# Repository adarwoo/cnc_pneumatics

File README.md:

# cnc_pneumatic
HUB for Masso based CNC to control the pneumatics of the CNC with 1 controller which implements the logic controller, and 1 hub, which handled all the pneumatic valves.

The PCB is double sided with a ATMEL attiny1626 microcontroller in the controller and a 824 in the hub.

This simple project is for my CNC which now has a pneumatic door (operated by pneumatic cylinders) and a pneumatic valve.
The valve is a 5/3 solenoid with an exhaust center.
This means than the solenoid takes 2 inputs:
- To push the cylinder
- To pull the cylinder
- If both are on - nothing happend
- When both are off - the pressure drops in the cylinder which can be freely moved (manual door opening/closing)

A pair of microswitch/proximity sensor detect when the door is fully opened and fully closed.

The intention is to use an ATTiny microcontroller.

The firwmware is using a priority based round-robin reactor and a C++ template based state machine - the boost SML.

It will be coded in C++2017 using the avr-gcc compiler.

## The project can compile in AVR Studio, but also on a Linux box, or Windows PC.

## Draft notes:

### States
The state machine should have the following states:

- Initial
  - From boot
- Unknown
  - Door is in the air (not in closed nor fully opened position)
- Opened
  - The door is resting in the opened position. From there, it can only be closed
- Closed
  - The door is resting fully closed.
- Opening
  - The solenoid 'push' is on, and the cylinder is expected to push the door open
- Closing
  - The 'pull' solenoid is on and the cylinder is expected to pull the door closed

### Events (transitions)

- OnOpen
  - The filtered open signal goes from low to high
- OnClose
  - The open signal goes from high to low
- DoorIsUp : Upper door sensor (filtered) goes high (from low)
- DoorIsDown : Lower door sensor goes high (from low)
- Timeout : A valid timer has expired

### Actions (thing to do in states or transition)

- Push : Turn on the solenoid valve controlling the push motion of the cylinder
- Pull : Turn on the solenoid valve controlling the pull motion of the cylinder
- StartTimer : Start the timer which limits to time to wait for a cycle completion (open/close)
- ResetTimer : Invalidate any ongoing timer so when the timer expires, it does nothing
- Release : Turn off the solenoid valve (push and pull)

**Note:** Since the operation is managed by a reactor, there are no race conditions.

```mermaid
---
title: Door control
---
stateDiagram-v2

   unknown --> opened  : door_is_up
   unknown --> closed  : door_is_down
   closed  --> opening : open / push_on
   opened  --> closing : close
   opening --> opening : door_moving_up
   opening --> unknown : timeout
   opening --> opened  : door_is_up
   closing --> closing : door_moving_down
   closing --> unknown : timeout
   closing --> closed  : door_is_down
```

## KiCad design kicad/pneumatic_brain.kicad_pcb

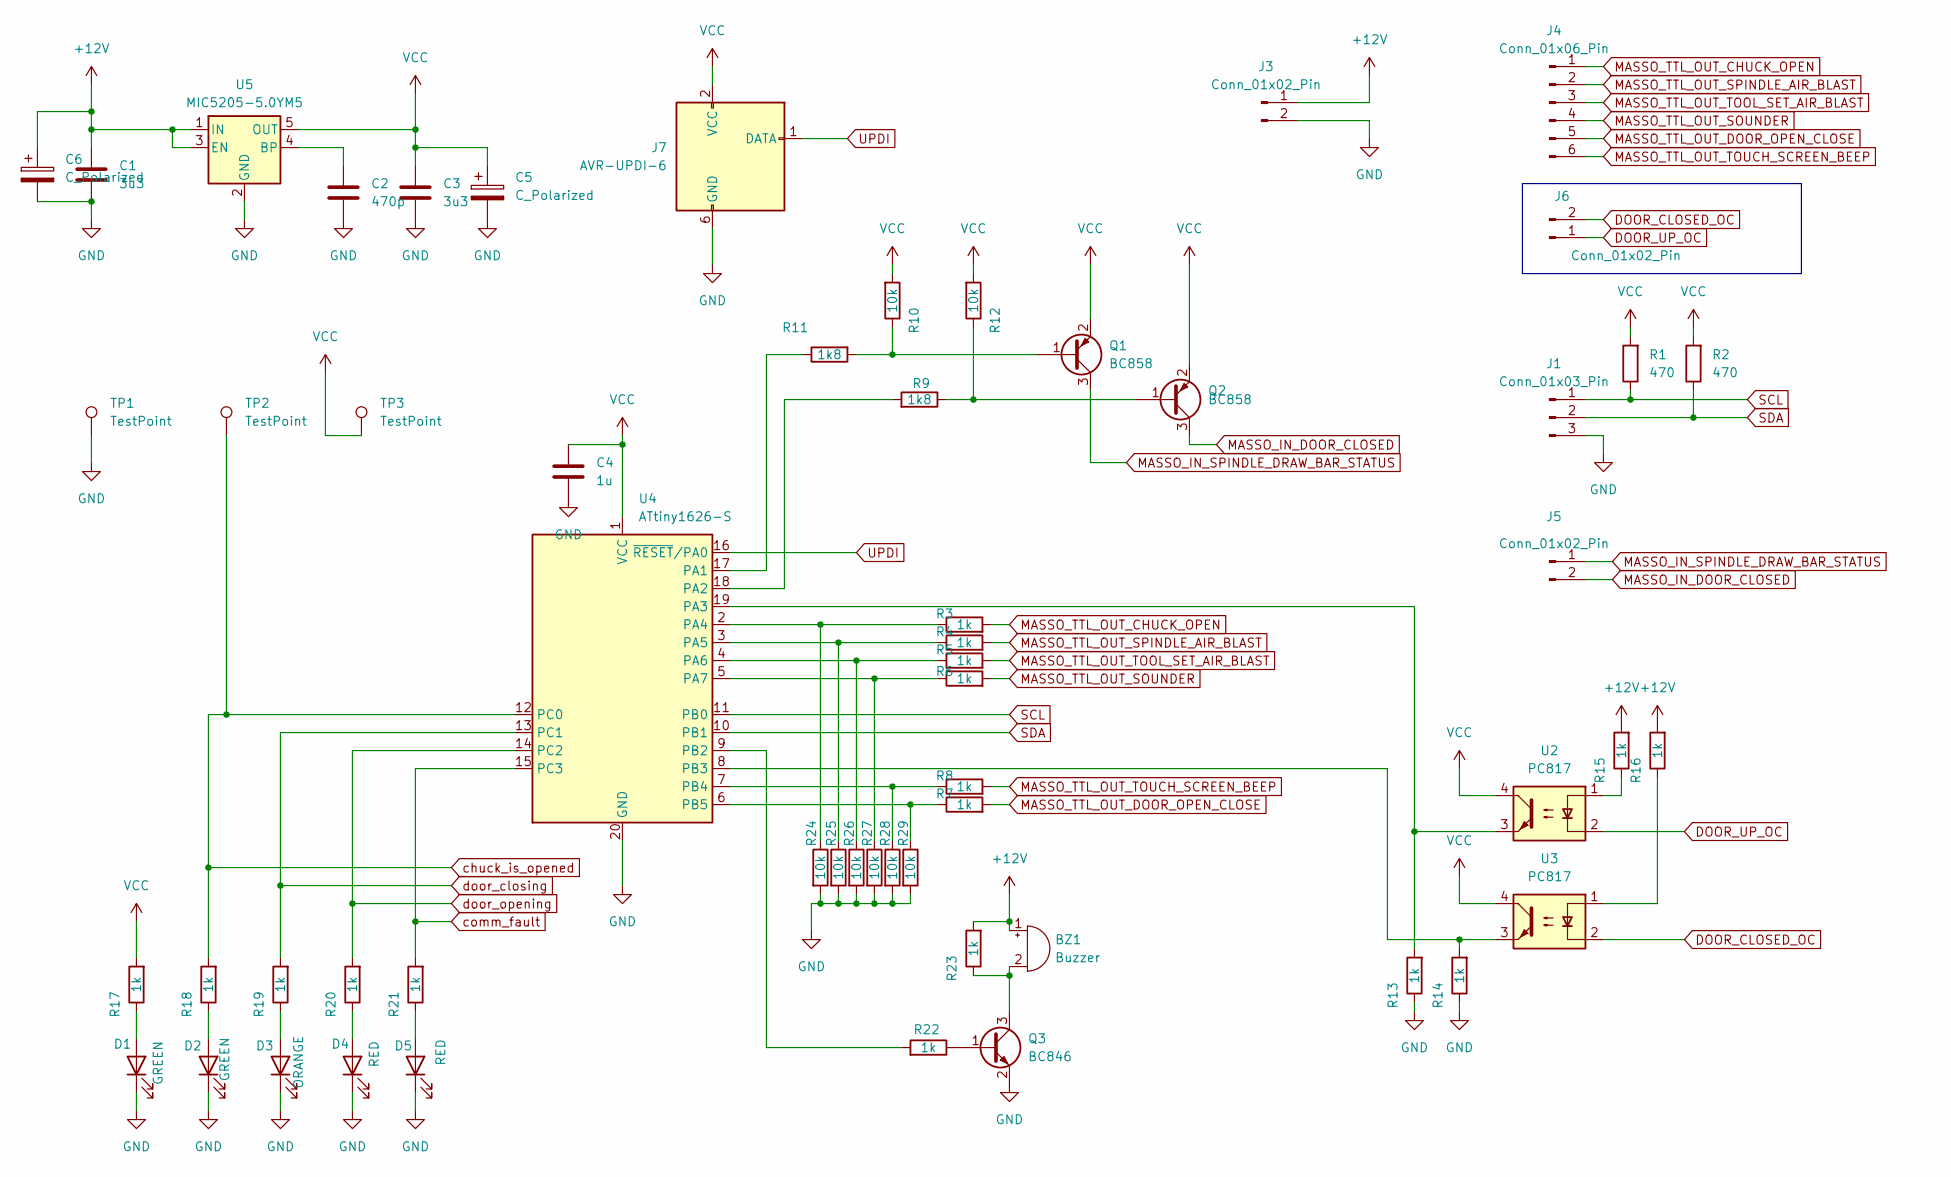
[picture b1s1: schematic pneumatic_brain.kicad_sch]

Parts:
BZ1: Buzzer; Buzzer_15x7.5RM7.6
C1, C3: 3u3; C_1206_3216Metric_Pad1.33x1.80mm_HandSolder
C2: 470p; C_0805_2012Metric_Pad1.18x1.45mm_HandSolder
C4: 1u; C_0805_2012Metric_Pad1.18x1.45mm_HandSolder
C5, C6: C_Polarized; C_1210_3225Metric_Pad1.33x2.70mm_HandSolder
D1, D2: GREEN; LED_D3.0mm
D3: ORANGE; LED_D3.0mm
D4, D5: RED; LED_D3.0mm
J1: Conn_01x03_Pin; PhoenixContact_MCV_1,5_3-G-3.81_1x03_P3.81mm_Vertical
J3, J5, J6: Conn_01x02_Pin; PhoenixContact_MCV_1,5_2-G-3.81_1x02_P3.81mm_Vertical
J4: Conn_01x06_Pin; PhoenixContact_MCV_1,5_6-G-3.81_1x06_P3.81mm_Vertical
J7: AVR-UPDI-6; PinHeader_2x03_P2.54mm_Vertical
Q1, Q2: BC858; SOT-23
Q3: BC846; SOT-23
R1, R2: 470; R_1206_3216Metric_Pad1.30x1.75mm_HandSolder
R3, R4, R5, R6, R7, R8, R13, R14, R15, R16, R17, R18, R19, R20, R21, R22, R23: 1k; R_1206_3216Metric_Pad1.30x1.75mm_HandSolder
R9, R11: 1k8; R_1206_3216Metric_Pad1.30x1.75mm_HandSolder
R10, R12, R24, R25, R26, R27, R28, R29: 10k; R_1206_3216Metric_Pad1.30x1.75mm_HandSolder
TP1, TP2, TP3: TestPoint; TestPoint_Loop_D2.60mm_Drill1.6mm_Beaded
U2, U3: PC817; DIP-4_W7.62mm
U4: ATtiny1626-S; SOIC-20W_7.5x12.8mm_P1.27mm
U5: MIC5205-5.0YM5; SOT-23-5

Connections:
+12V: BZ1.1 (+), C1.1, C6.1, J3.1, R15.2, R16.2, R23.2, U5.1 (IN), U5.3 (EN)
DOOR_CLOSED_OC: J6.2, U3.2
DOOR_UP_OC: J6.1, U2.2
GND: C1.2, C2.2, C3.2, C4.2, C5.2, C6.2, D1.1 (K), D2.1 (K), D3.1 (K), D4.1 (K), D5.1 (K), J1.3, J3.2, J7.6 (GND), Q3.2 (E), R13.1, R14.1, R24.2, R25.2, R26.2, R27.2, R28.2, R29.2, TP1.1, U4.20 (GND), U5.2 (GND)
MASSO_IN_DOOR_CLOSED: J5.2, Q2.3 (C)
MASSO_IN_SPINDLE_DRAW_BAR_STATUS: J5.1, Q1.3 (C)
MASSO_TTL_OUT_CHUCK_OPEN: J4.1, R3.2
MASSO_TTL_OUT_DOOR_OPEN_CLOSE: J4.5, R7.2
MASSO_TTL_OUT_SOUNDER: J4.4, R6.2
MASSO_TTL_OUT_SPINDLE_AIR_BLAST: J4.2, R4.2
MASSO_TTL_OUT_TOOL_SET_AIR_BLAST: J4.3, R5.2
MASSO_TTL_OUT_TOUCH_SCREEN_BEEP: J4.6, R8.2
unnamed: BZ1.2 (-), Q3.3 (C), R23.1
unnamed: D1.2 (A), R17.1
unnamed: D2.2 (A), R18.1
unnamed: D3.2 (A), R19.1
unnamed: D4.2 (A), R20.1
unnamed: D5.2 (A), R21.1
unnamed: Q1.1 (B), R10.1, R11.2
unnamed: Q2.1 (B), R9.1, R12.1
unnamed: Q3.1 (B), R22.1
unnamed: R15.1, U2.1
unnamed: R16.1, U3.1
unnamed: R11.1, U4.17 (PA1)
unnamed: R9.2, U4.18 (PA2)
unnamed: R13.2, U2.3, U4.19 (PA3)
unnamed: R3.1, R24.1, U4.2 (PA4)
unnamed: R4.1, R25.1, U4.3 (PA5)
unnamed: R5.1, R26.1, U4.4 (PA6)
unnamed: R6.1, R27.1, U4.5 (PA7)
unnamed: R22.2, U4.9 (PB2)
unnamed: R14.2, U3.3, U4.8 (PB3)
unnamed: R8.1, R28.1, U4.7 (PB4)
unnamed: R7.1, R29.1, U4.6 (PB5)
unnamed: C2.1, U5.4 (BP)
SCL: J1.1, R1.1, U4.11 (PB0)
SDA: J1.2, R2.1, U4.10 (PB1)
UPDI: J7.1 (DATA), U4.16 (~RESET/PA0)
VCC: C3.1, C4.1, C5.1, J7.2 (VCC), Q1.2 (E), Q2.2 (E), R1.2, R2.2, R10.2, R12.2, R17.2, TP3.1, U2.4, U3.4, U4.1 (VCC), U5.5 (OUT)
chuck_is_opened: R18.2, TP2.1, U4.12 (PC0)
comm_fault: R21.2, U4.15 (PC3)
door_closing: R19.2, U4.13 (PC1)
door_opening: R20.2, U4.14 (PC2)

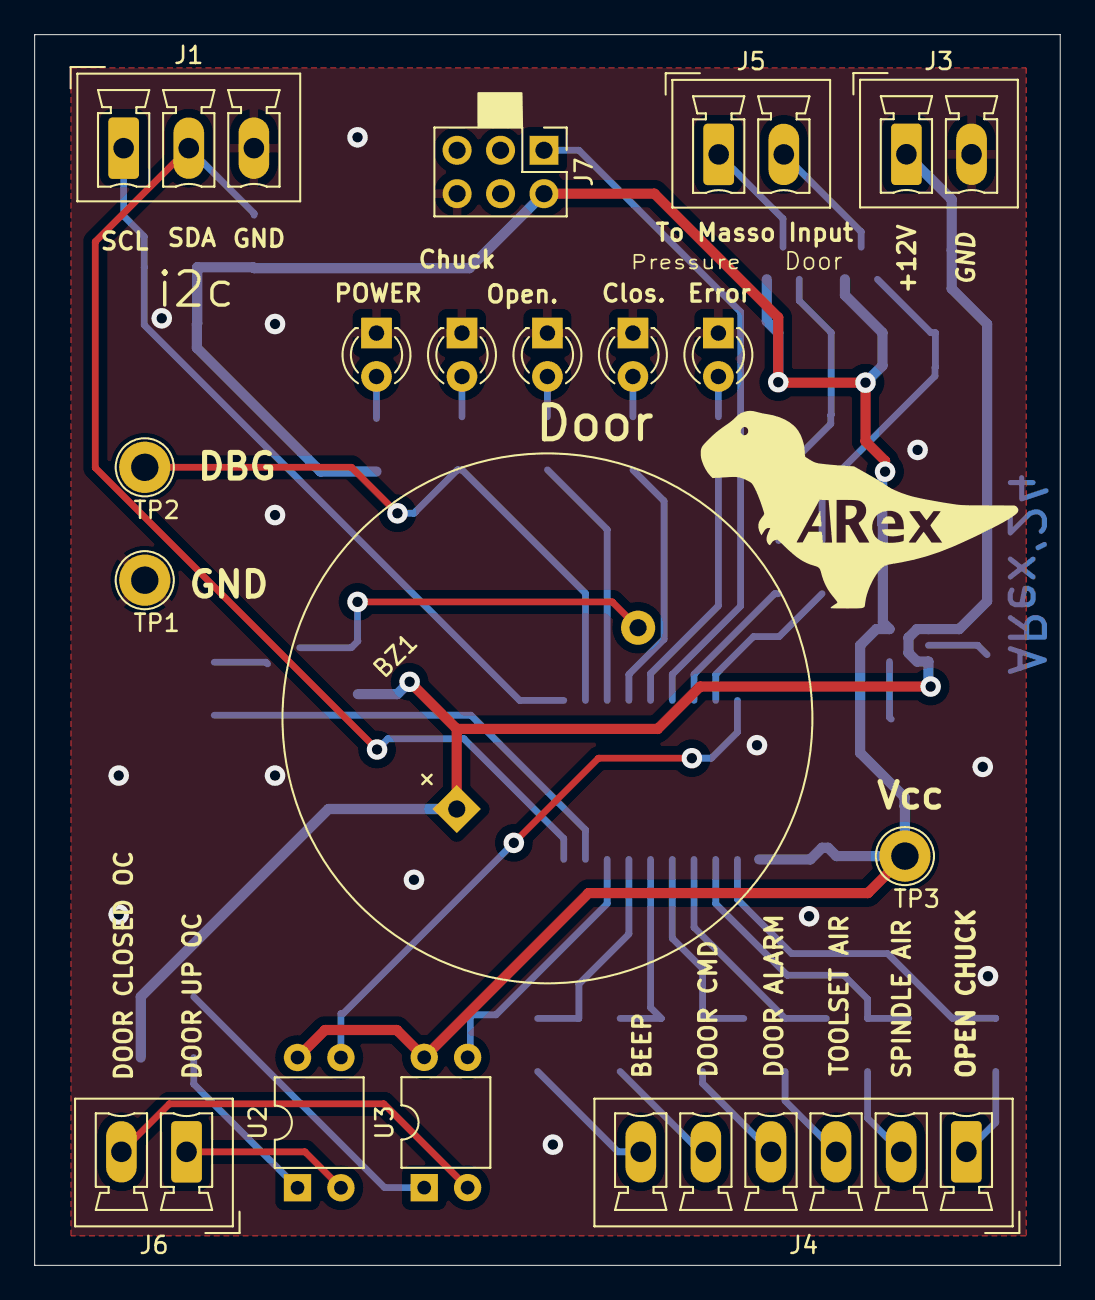
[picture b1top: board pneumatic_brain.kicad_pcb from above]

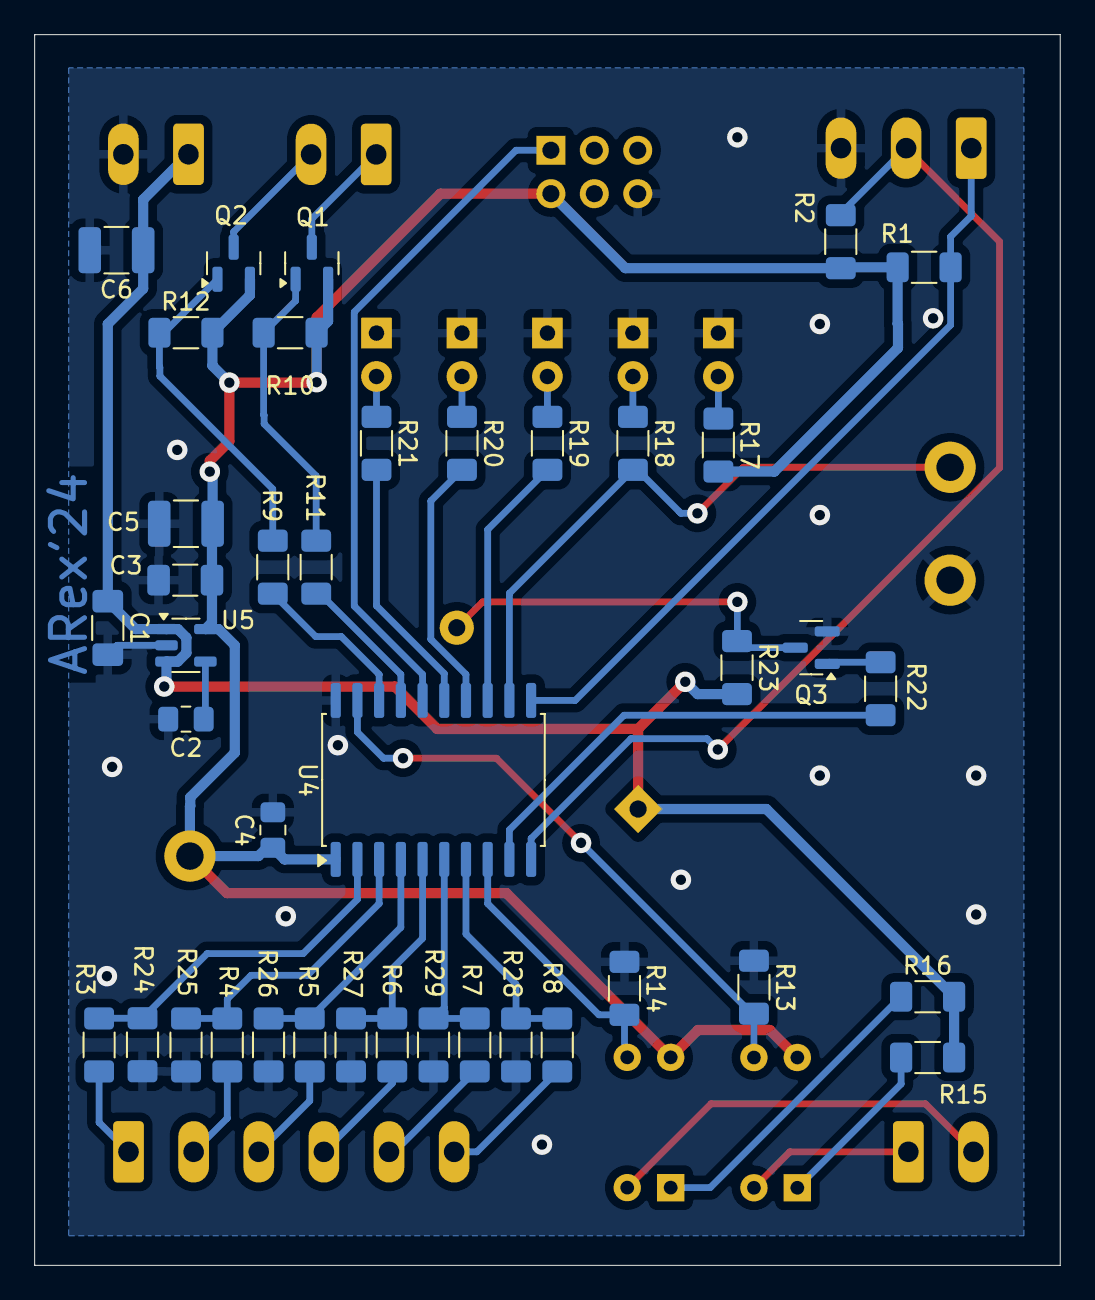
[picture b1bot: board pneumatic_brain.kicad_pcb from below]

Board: 2 copper layers, 60.0 x 72.0 mm, 57 parts (40 on the bottom side), 43 nets.

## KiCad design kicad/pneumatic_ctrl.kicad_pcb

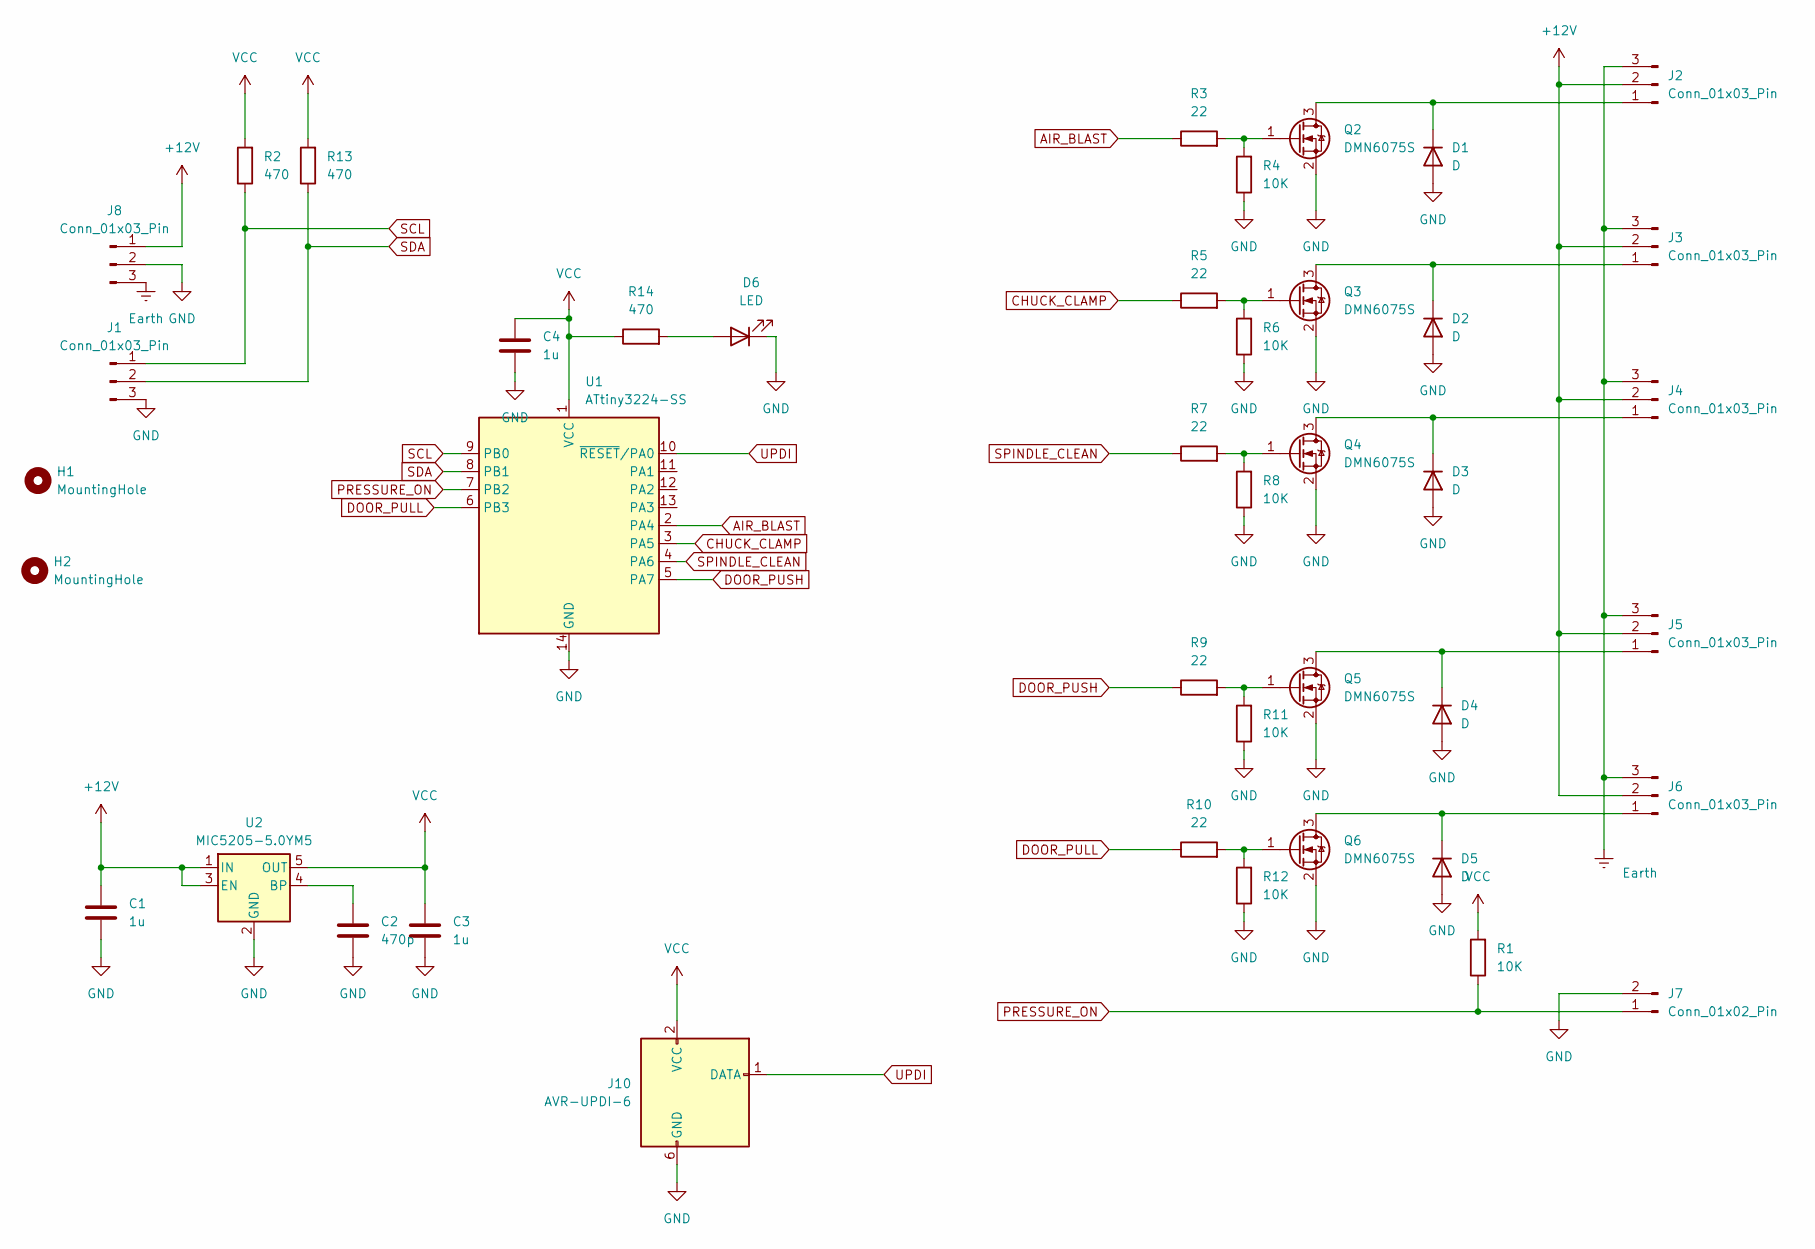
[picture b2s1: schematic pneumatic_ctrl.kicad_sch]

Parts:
C1, C3, C4: 1u; C_1206_3216Metric_Pad1.33x1.80mm_HandSolder
C2: 470p; C_0805_2012Metric_Pad1.18x1.45mm_HandSolder
D1, D2, D3, D4, D5: D; D_MicroSMP_AK
D6: LED; LED_D3.0mm
H1, H2: MountingHole; MountingHole_3.2mm_M3_DIN965
J1, J2, J3, J4, J5, J6, J8: Conn_01x03_Pin; PhoenixContact_MCV_1,5_3-G-3.81_1x03_P3.81mm_Vertical
J7: Conn_01x02_Pin; PhoenixContact_MCV_1,5_2-G-3.81_1x02_P3.81mm_Vertical
J10: AVR-UPDI-6; PinHeader_2x03_P2.54mm_Vertical
Q2, Q3, Q4, Q5, Q6: DMN6075S; SOT-23
R1, R4, R6, R8, R11, R12: 10K; R_1206_3216Metric_Pad1.30x1.75mm_HandSolder
R2, R13, R14: 470; R_1206_3216Metric_Pad1.30x1.75mm_HandSolder
R3, R5, R7, R9, R10: 22; R_1206_3216Metric_Pad1.30x1.75mm_HandSolder
U1: ATtiny3224-SS; SOIC-14_3.9x8.7mm_P1.27mm
U2: MIC5205-5.0YM5; SOT-23-5

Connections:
+12V: C1.1, J2.2, J3.2, J4.2, J5.2, J6.2, J8.1, U2.1 (IN), U2.3 (EN)
AIR_BLAST: R3.1, U1.2 (PA4)
CHUCK_CLAMP: R5.1, U1.3 (PA5)
DOOR_PULL: R10.1, U1.6 (PB3)
DOOR_PUSH: R9.1, U1.5 (PA7)
Earth: J2.3, J3.3, J4.3, J5.3, J6.3, J8.3
GND: C1.2, C2.2, C3.2, C4.2, D1.2 (A), D2.2 (A), D3.2 (A), D4.2 (A), D5.2 (A), D6.1 (K), J1.3, J7.2, J8.2, J10.6 (GND), Q2.2 (S), Q3.2 (S), Q4.2 (S), Q5.2 (S), Q6.2 (S), R4.1, R6.1, R8.1, R11.1, R12.1, U1.14 (GND), U2.2 (GND)
unnamed: D1.1 (K), J2.1, Q2.3 (D)
unnamed: D2.1 (K), J3.1, Q3.3 (D)
unnamed: D3.1 (K), J4.1, Q4.3 (D)
unnamed: D4.1 (K), J5.1, Q5.3 (D)
unnamed: D5.1 (K), J6.1, Q6.3 (D)
unnamed: D6.2 (A), R14.2
unnamed: Q2.1 (G), R3.2, R4.2
unnamed: Q3.1 (G), R5.2, R6.2
unnamed: Q4.1 (G), R7.2, R8.2
unnamed: Q5.1 (G), R9.2, R11.2
unnamed: Q6.1 (G), R10.2, R12.2
unnamed: C2.1, U2.4 (BP)
PRESSURE_ON: J7.1, R1.1, U1.7 (PB2)
SCL: J1.1, R2.1, U1.9 (PB0)
SDA: J1.2, R13.1, U1.8 (PB1)
SPINDLE_CLEAN: R7.1, U1.4 (PA6)
UPDI: J10.1 (DATA), U1.10 (~RESET/PA0)
VCC: C3.1, C4.1, J10.2 (VCC), R1.2, R2.2, R13.2, R14.1, U1.1 (VCC), U2.5 (OUT)

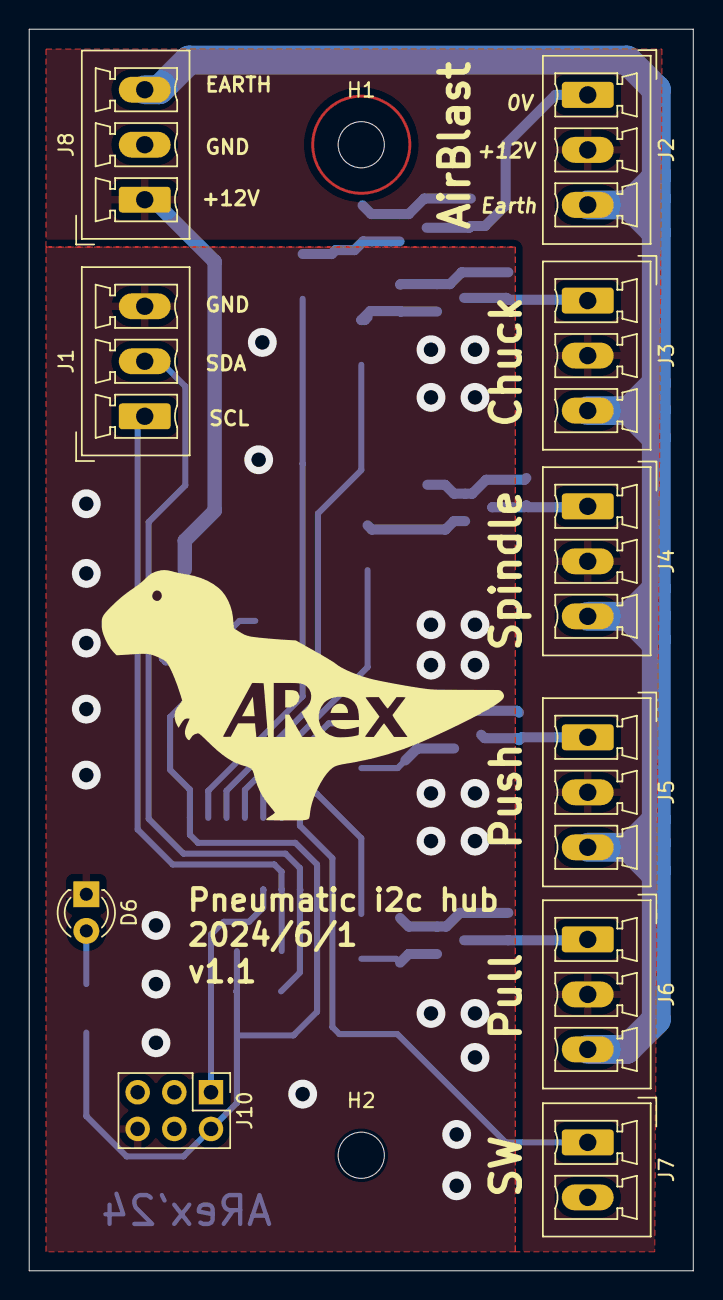
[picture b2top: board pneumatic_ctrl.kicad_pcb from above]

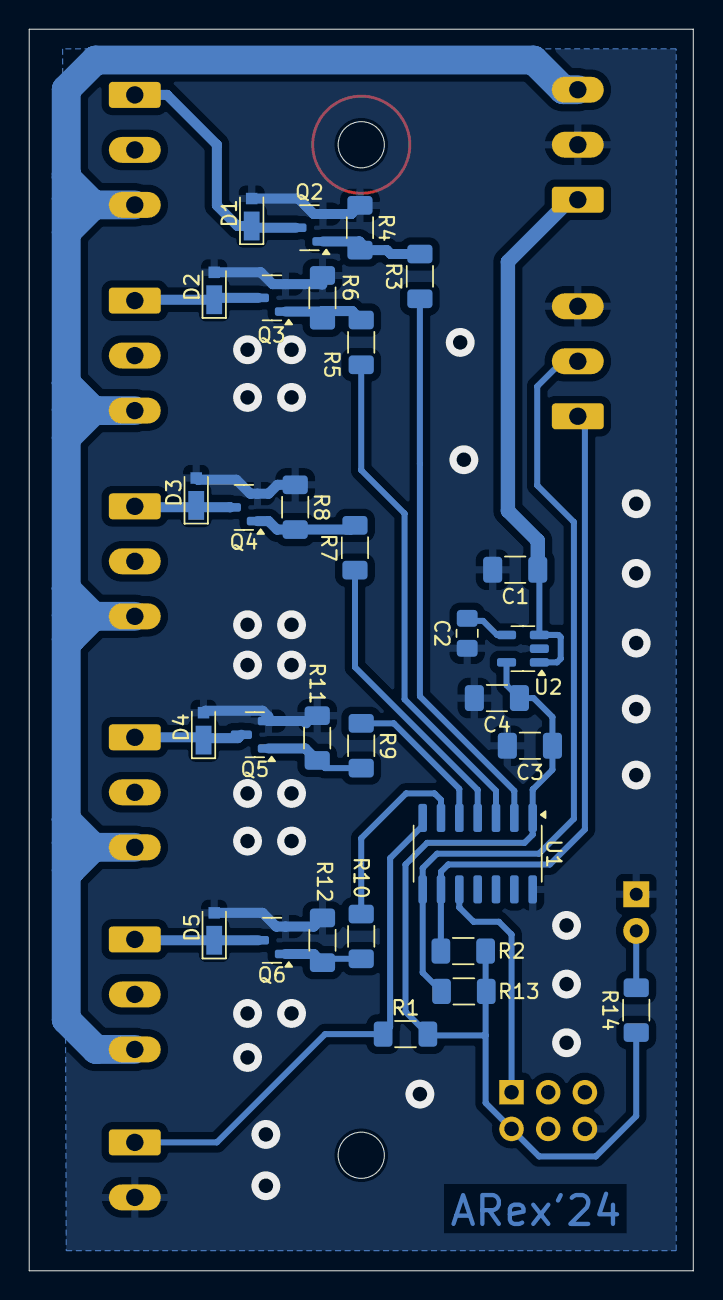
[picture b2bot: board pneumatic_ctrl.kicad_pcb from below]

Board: 2 copper layers, 46.0 x 86.0 mm, 42 parts (30 on the bottom side), 25 nets.

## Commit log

2024-05-02 Update README.md
    Initial description
2024-05-02 Update README.md
    Adding state diagram
2024-05-24 Initial release
2024-05-24 Update README.md
    Renamed the project
2024-05-26 Removing object files from the scope
2024-05-26 Removign maps too
2024-05-26 Unified ready to test
2024-05-28 Fixed many small but import bug. Added boost. Code is complete, testing in progress
2024-06-02 Hub is working
2024-06-03 New binaries
2024-06-03 Spotted an issue trying to cancel a repeating timer
2024-06-20 Tested on the bench and working
2024-06-22 Fixed dependencies and debug flags
2024-06-22 Clean up
2024-06-22 Fixed ignore
2024-06-22 Deleting unused
2024-06-22 Fixed a big bug in the reactor and enabled CRC check of the entire flash. Added a Dockerfile to compile in docker
2024-06-24 Fixed reactor size for tiny apps
2024-06-25 Cleaning up the build
2024-06-25 Adding sast
2024-06-25 Added CI for analysis
2024-06-26 Adding CI
2024-08-18 Speeding up reactor for the timer to reduce interrupt exection time
2024-08-19 Add modbus as a child
2024-10-02 About to break all
2024-10-25 On going
2024-10-25 CRC to be added
2024-10-29 Splitting states in 2 stages
2024-10-29 Generation requires testing
2024-10-29 Generation complete
2024-10-29 Fixed formatting
2024-11-01 Integrating the SM in the genrated code
2024-11-12 UART frame tx is working
2024-11-14 Working on the sm
2024-11-15 Compiles.
2024-11-25 Compiling but not running
2024-11-25 Added simulation
2024-11-26 Fixed the vaargs and got a response
2024-11-26 Added the logger for the simulation part
2024-11-26 Automatic commit
2024-11-26 Logger licence update
2024-11-27 Modbus working for simple commands
2024-11-27 Fixed generator
2024-11-27 Removed ccp in c
2024-11-28 Prepared the modbus for the console
2024-11-29 Working on the ioport
2024-12-03 IOPort strategy working?
2024-12-04 Automatic update
2024-12-04 Using the asx ioport. Saved 1kbytes!
2024-12-05 Automatic upload
2024-12-12 Working on the console
